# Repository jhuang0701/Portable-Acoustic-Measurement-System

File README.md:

# Portable Acoustic Measurement System

A portable acoustic measurement instrument I designed, built and validated: an electret-microphone analog front end on a custom 2-layer KiCad board, an ESP32 sampling at 80 kSPS, and an automated Python hardware-in-the-loop test that checks the board against its design calculations.

## Highlights

- **Analog front end, designed from scratch:** electret capsule bias network, OPA2365 preamp with four switchable gains (TMUX1104), and a 4th-order Sallen-Key anti-alias filter (calculated -3 dB at 25.5 kHz), hand-routed on a 2-layer mixed-signal PCB.
- **Root-caused an 8.6 dB measurement error to the ESP32 ADC.** The continuous-mode driver returns every sample pair swapped. Undoing the swap brought the measured filter response within 0.37 dB of calculation through 25 kHz, and the test now checks sample order automatically before every run.
- **Automated hardware-in-the-loop validation:** `hil_sweep.py` drives the board over serial, sweeps 1 to 55 kHz, and compares each point against the calculation and a Monte Carlo tolerance band. At gain x100 the response sat inside the band at every point, within 0.35 dB of calculation up to 25 kHz.
- **End-to-end test on real sound:** with a phone as the source, measured level fell -5.46 dB per doubling of distance (inverse-square law predicts -6.02 dB), and 500 Hz to 4 kHz tones read within 0.014% of frequency, against pass criteria fixed before the data were taken.

*Gain 2, 22 Nov run. Red: samples as the ESP32 delivers them. Blue: after the pair swap-back. Generated from the saved per-capture log by [`plot_swap_effect.py`](validation/hil/plot_swap_effect.py); no value is re-measured.*

## Signal chain

WM-61B capsule -> bias network -> OPA2365 preamp with TMUX1104 gain select (nominal gains 1, 10.1, 101, 1001) -> two Sallen-Key low-pass sections (calculated -3 dB at 25.5 kHz) -> ESP32 ADC on GPIO34, 80 kSPS, continuous mode.

Test points on the board: TP1 MIC_OUT, TP2 MIC_IN, TP3 VREF, TP4 PRE_OUT, TP5 O1, TP6 ADC_IN, TP7 VCCA, TP8 GND.

## Validation status in detail

Every number here was measured and compared against a calculation. Full tables and the status of each result are in [docs/results.md](docs/results.md).

| Result | Status |
|---|---|
| ESP32 ADC returns sample pairs swapped; swap-back verified; checked automatically at the start of every run | VALID |
| Filter response at gain 2, 1 to 55 kHz vs calculation: inside the tolerance band at all 9 points on three runs (22 Nov), within 0.35 dB up to 25 kHz and 0.78 dB at worst; two later runs (23 Nov) were worse, up to 1.9 dB | PROVISIONAL: the injected signal level drifted between days |
| The 23 Nov drift is upstream of the filter (above 5 kHz the tone is lower by a nearly constant factor, with the same 5 to 55 kHz shape as on 22 Nov) | diagnosis, cause not found |
| Gain steps, noise, dynamic range from earlier manual runs | PROVISIONAL |
| End to end with a phone sound source, noise band 891 to 1122 Hz at 10/20/30 cm: level fell -5.46 dB per doubling of distance (expected -6.02, limit +/-1.5), 10 cm repeat -0.33 dB, 35.5 dB above silence | VALID for this scope: relative level, one room, one pass |
| End to end, tone frequency (500, 1000, 2000, 4000 Hz from a phone) read within 0.014 % | VALID, from a separate run; phone frequency not independently calibrated |
| Pure 1 kHz tone level test in a room | did not give a stable result in four real runs (room reflections); replaced by the noise-band test, all runs kept in `validation/hil/acoustic_results/` |
| Gain 1 and gain 3 filter response | NOT MEASURED |

The plot above is one run. The later runs that disagree are published beside it in [docs/results.md](docs/results.md), not hidden.

## Repository layout

| Path | What is in it |
|---|---|
| `validation/hil/` | Automated hardware-in-the-loop test: firmware (`acoustic_hil/acoustic_hil.ino`), `hil_sweep.py`, config generator, mock board, README |
| `validation/hil/results/` | Every hardware run: plot, per-capture log, summary and metadata, including bad runs |
| `validation/hil/acoustic_results/` | Every real end-to-end acoustic run (phone as sound source), including the failed and inconclusive ones |
| `docs/results.md` | Measured vs calculated, with status |
| `docs/img/` | Figures used in this README |
| `docs/lessons-learned.md` | What went wrong and what was learned |
| `docs/known-issues.md` | Open problems, what was not measured, ideas for a second revision |
| `hardware/photos/` | Photos of the assembled board: top-down and angled views |
| `hardware/` | KiCad project, schematic and layout |

## Running the validation

See [validation/hil/README.md](validation/hil/README.md). Short version: upload the firmware with Flash Mode DIO and Flash Frequency 40 MHz, close the Serial Monitor, connect GPIO25 -> 100 kohm -> TP2 and a 100 ohm resistor to TP3 (capsule unplugged), then:

```
python3 hil_sweep.py --port /dev/cu.usbserial-0001 --gains 2 --reps 3 --countdown 15 --baud 115200 --n-samples 8192 --settle-ms 300
```

`python3 hil_sweep.py --port mock` runs against a simulated board. Output from the mock is watermarked and is never a measurement.

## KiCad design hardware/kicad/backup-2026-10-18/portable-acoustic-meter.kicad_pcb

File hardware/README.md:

# Hardware files

- [KiCad project](kicad/)
- [Schematic PDF](docs/portable-acoustic-meter-schematic.pdf)

## PCB views

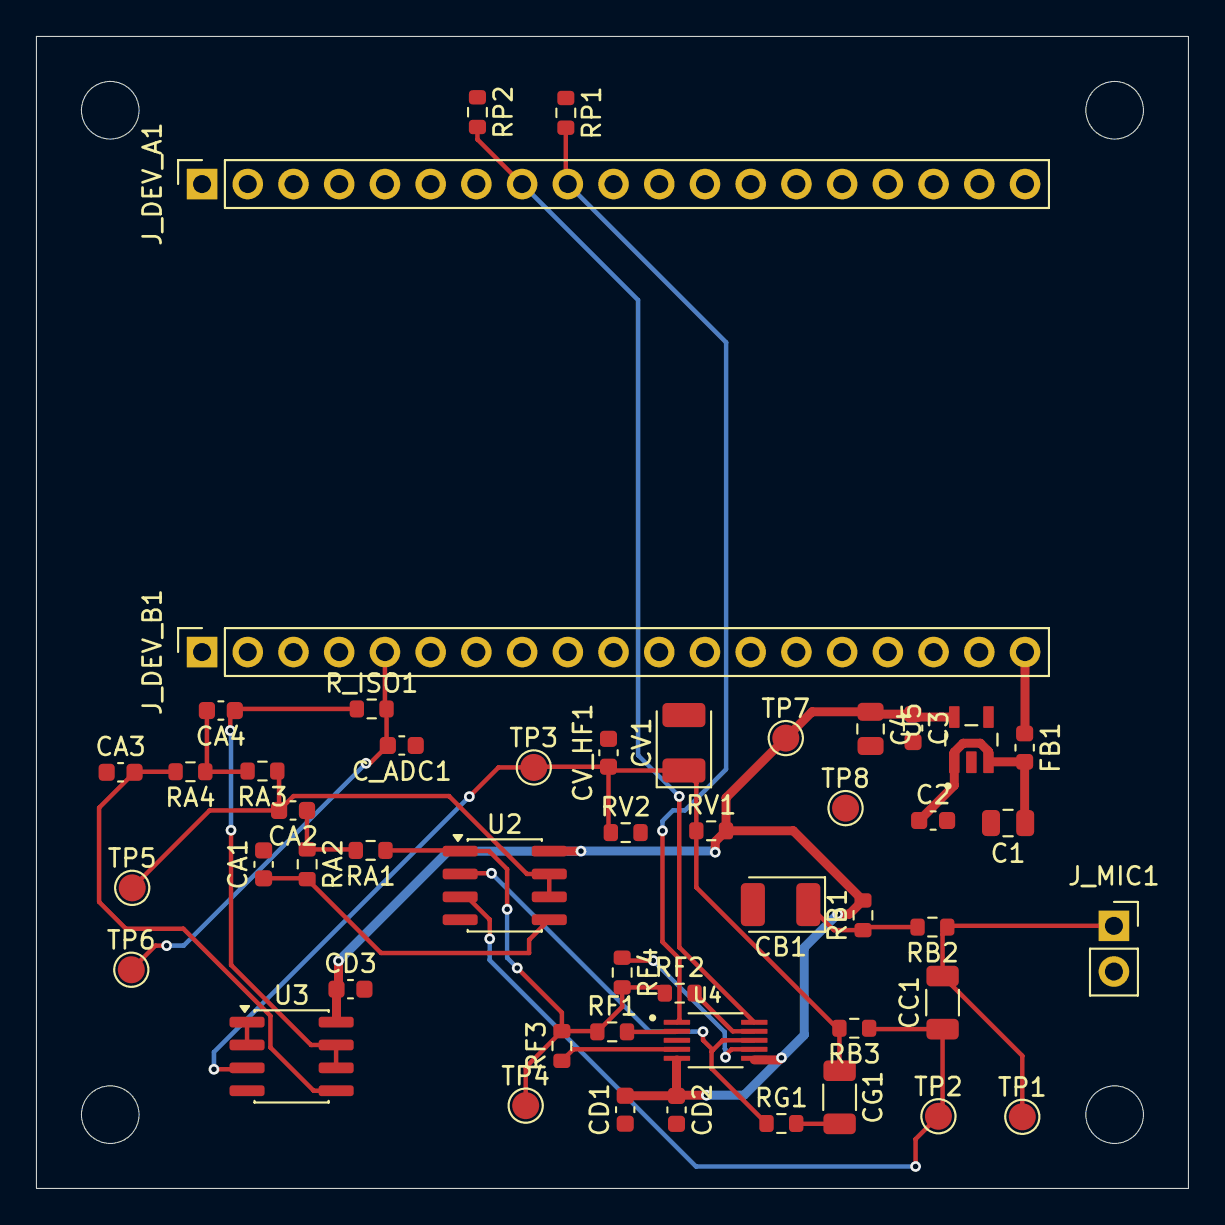
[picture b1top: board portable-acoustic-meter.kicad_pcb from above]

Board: 2 copper layers, 64.0 x 64.0 mm, 50 parts (0 on the bottom side), 25 nets.

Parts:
C1, C4: 10µF; C_0805_2012Metric
C2, C3: 1µF; C_0603_1608Metric
CA1, CA2, CA3: 470pF; C_0603_1608Metric
CA4: 3.3nF; C_0603_1608Metric
CB1: 100µF; CP_EIA-3528-21_Kemet-B
CC1: 1µF; C_1206_3216Metric
CD1, CD2, CD3: 100nF; C_0603_1608Metric
CG1: 47µF; C_1206_3216Metric
CV1: 100µF; CP_EIA-3528-21_Kemet-B
CV_HF1: 100nF; C_0603_1608Metric
C_ADC1: 100nF; C_0603_1608Metric
FB1: 600Ω; L_0603_1608Metric
J_DEV_A1: Conn_01x19; PinSocket_1x19_P2.54mm_Vertical
J_DEV_B1: Conn_01x19; PinSocket_1x19_P2.54mm_Vertical
J_MIC1: Conn_01x02; PinSocket_1x02_P2.54mm_Vertical
RA1, RA2: 12kΩ; R_0603_1608Metric
RA3, RA4: 5.1kΩ; R_0603_1608Metric
RB1: 470Ω; R_0603_1608Metric
RB2: 2.2kΩ; R_0603_1608Metric
RB3: 47kΩ; R_0603_1608Metric
RF1: 0Ω; R_0603_1608Metric
RF2: 9.1kΩ; R_0603_1608Metric
RF3: 100kΩ; R_0603_1608Metric
RF4: 1MΩ; R_0603_1608Metric
RG1: 1kΩ; R_0603_1608Metric
RP1, RP2: 100kΩ; R_0603_1608Metric
RV1: 1.2kΩ; R_0603_1608Metric
RV2: 1kΩ; R_0603_1608Metric
R_ISO1: 10Ω; R_0603_1608Metric
TP1, TP2, TP3, TP4, TP5, TP6, TP7, TP8: TestPoint; TestPoint_Pad_D1.5mm
U2, U3: OPA2365A; SOIC-8_3.9x4.9mm_P1.27mm
U4: TMUX1104DGSR; SOP50P490X110-10N
U5: TPS7A2033PDBVR; SOT95P280X145-5N

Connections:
/5V_A: C1.1, C2.1, FB1.2, U5.1 (IN), U5.3 (EN)
/5V_DEV: FB1.1, J_DEV_B1.19
/A1: CA2.1, RA1.2, RA2.1
/A2: CA4.2, RA3.2, RA4.1
/ADC_IN: C_ADC1.2, J_DEV_B1.5, R_ISO1.2, TP6.1 (1_1)
/B1: CA1.1, RA2.2, U2.5 (+)
/B2: CA3.2, RA4.2, U3.5 (+)
/G: CG1.2, RG1.2
/GAIN_A0: J_DEV_A1.9, RP1.2, U4.1 (A0)
/GAIN_A1: J_DEV_A1.8, RP2.2, U4.10 (A1)
/INV: RG1.1, U2.2 (-), U4.8 (D1)
/MIC_FILT: CB1.1, RB1.1, RB2.2
/MIC_IN: CC1.1, RB3.1, TP2.1 (1_1), U2.3 (+)
/MIC_OUT: CC1.2, J_MIC1.1, RB2.1, TP1.1 (1_1)
/O1: CA2.2, RA3.1, TP5.1 (1_1), U2.6 (-), U2.7
/O2: CA4.1, R_ISO1.1, U3.6 (-), U3.7
/PRE_OUT: RA1.1, RF1.1, RF2.1, RF3.2, RF4.2, TP4.1 (1_1), U2.1
/VCCA: C3.1, C4.1, CD1.2, CD2.1, CD3.1, RB1.2, RV1.2, TP7.1 (1_1), U2.8 (V+), U3.8 (V+), U4.5 (EN), U4.6 (VDD), U5.5 (OUT)
/VREF: CG1.1, CV1.1, CV_HF1.1, RB3.2, RV1.1, RV2.1, TP3.1 (1_1), U3.3 (+)
GND: C1.2, C2.2, C3.2, C4.2, CA1.2, CA3.1, CB1.2, CD1.1, CD2.2, CD3.2, CV1.2, CV_HF1.2, C_ADC1.1, J_DEV_A1.1, J_DEV_A1.7, J_DEV_B1.14, J_MIC1.2, RP1.1, RP2.1, RV2.2, TP8.1 (1_1), U2.4 (V-), U3.4 (V-), U4.3 (GND), U5.2 (GND)
unnamed: U3.1, U3.2 (-)
unnamed: RF1.2, U4.2 (S1)
unnamed: RF2.2, U4.9 (S2)
unnamed: RF3.1, U4.4 (S3)
unnamed: RF4.1, U4.7 (S4)
